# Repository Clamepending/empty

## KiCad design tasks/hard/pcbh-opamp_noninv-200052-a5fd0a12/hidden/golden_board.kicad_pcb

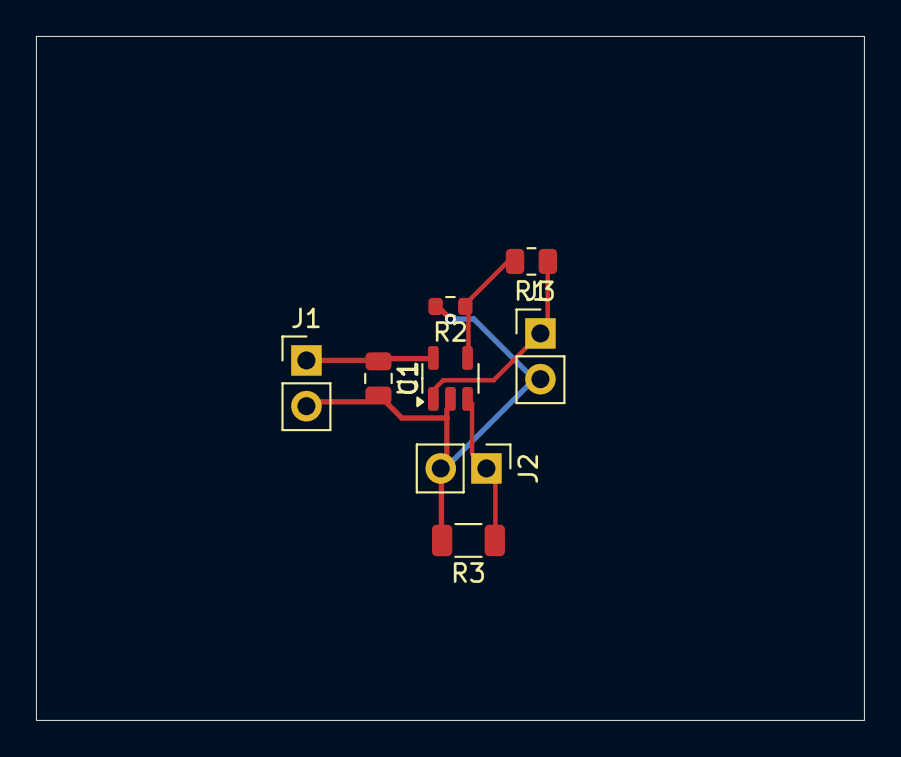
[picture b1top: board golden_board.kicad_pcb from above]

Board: 2 copper layers, 46.0 x 38.0 mm, 8 parts (0 on the bottom side), 5 nets.

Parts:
C1: 100n; C_0805_2012Metric
J1, J2, J3: PinHeader_1x02_P2.54mm_Vertical
R1: 15k; R_0805_2012Metric
R2: 7.5k; R_0603_1608Metric
R3: 1M; R_1206_3216Metric
U1: SOT-23-5

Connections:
FB: R1.2, R2.1, U1.4
GND: C1.2, J1.2, J2.2, J3.2, R2.2, R3.2, U1.2
IN: J2.1, R3.1, U1.3
OUT: J3.1, R1.1, U1.1
VCC: C1.1, J1.1, U1.5

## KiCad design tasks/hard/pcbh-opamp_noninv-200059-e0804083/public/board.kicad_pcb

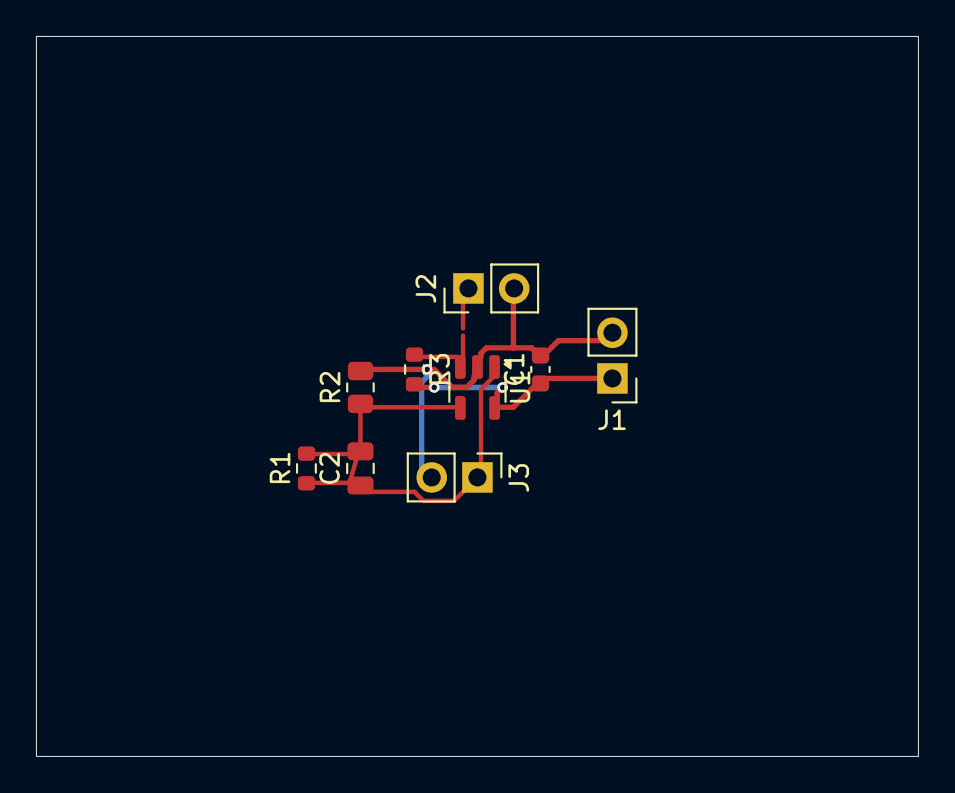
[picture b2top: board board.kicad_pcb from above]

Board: 2 copper layers, 49.0 x 40.0 mm, 9 parts (0 on the bottom side), 5 nets.

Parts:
C1: 100n; C_0603_1608Metric
C2: 470p; C_0805_2012Metric
J1, J2, J3: PinHeader_1x02_P2.54mm_Vertical
R1: 4.12k; R_0603_1608Metric
R2: 1.37k; R_0805_2012Metric
R3: 1M; R_0603_1608Metric
U1: SOT-23-5

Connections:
FB: C2.2, R1.2, R2.1, U1.4
GND: C1.2, J1.2, J2.2, J3.2, R2.2, U1.2
IN: J2.1, R3.1, U1.3
OUT: C2.1, J3.1, R1.1, U1.1
VCC: C1.1, J1.1, R3.2, U1.5
